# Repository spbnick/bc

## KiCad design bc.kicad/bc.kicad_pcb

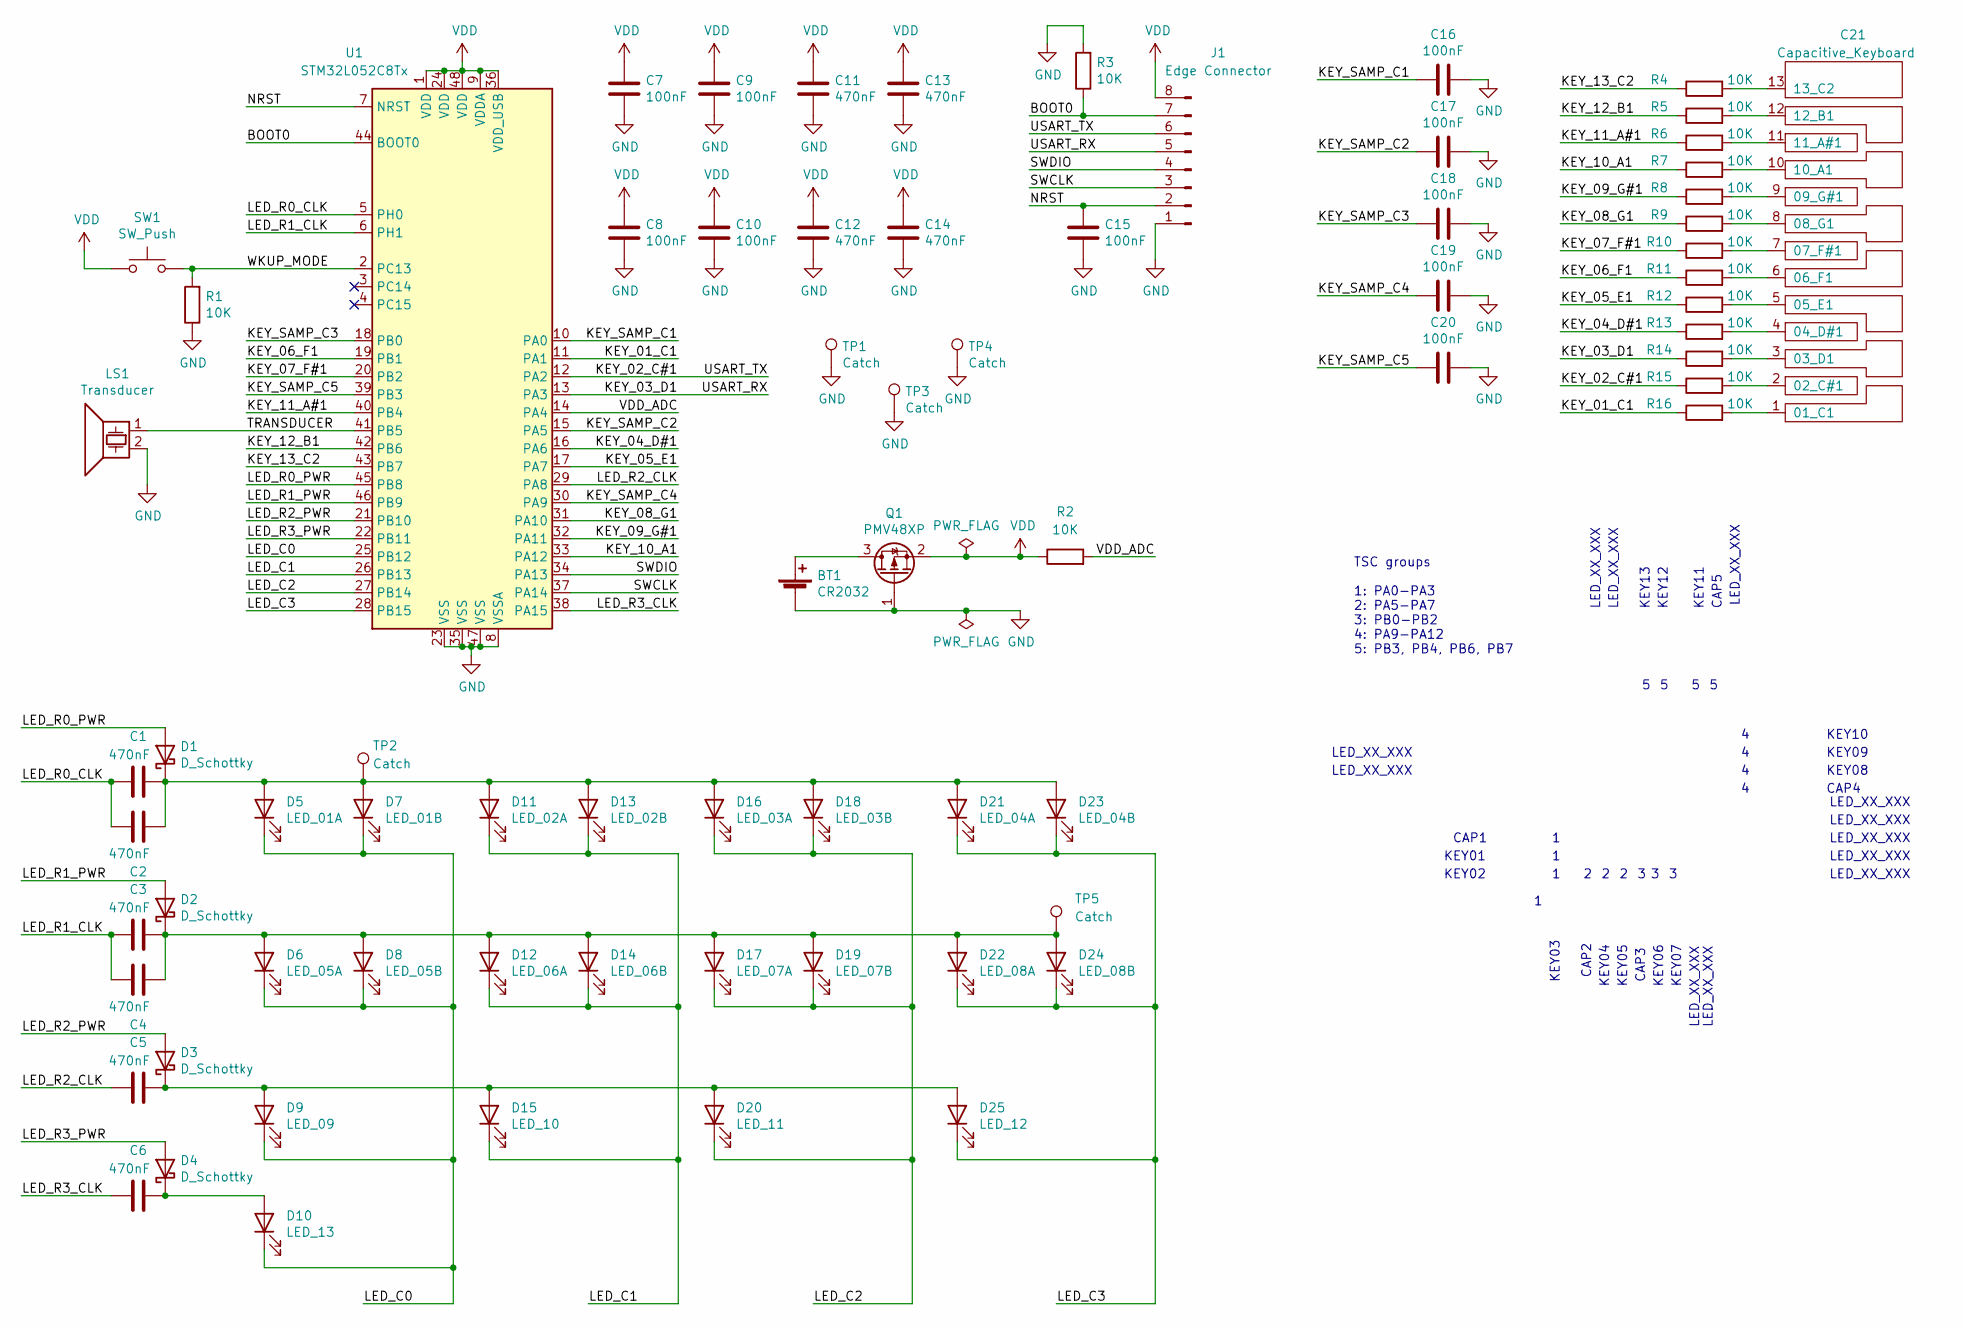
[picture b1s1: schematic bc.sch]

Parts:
BT1: CR2032; BatteryHolder_Keystone_3002_1x2032; LCSC C238099
C1, C2, C3, C4, C5, C6, C11, C12, C13, C14: 470nF; C_0402_1005Metric; LCSC C47339
C7, C8, C9, C10, C15, C16, C17, C18, C19, C20: 100nF; C_0402_1005Metric; LCSC C1525
C21: Capacitive_Keyboard; keyboard
D1, D2, D3, D4: D_Schottky; D_SOD-123; LCSC C8598
D5: LED_01A; side_led; Digi-Key 160-1870-1-ND
D6: LED_05A; side_led
D7: LED_01B; side_led
D8: LED_05B; side_led
D9: LED_09; side_led
D10: LED_13; side_led
D11: LED_02A; side_led
D12: LED_06A; side_led
D13: LED_02B; side_led
D14: LED_06B; side_led
D15: LED_10; side_led
D16: LED_03A; side_led
D17: LED_07A; side_led
D18: LED_03B; side_led
D19: LED_07B; side_led
D20: LED_11; side_led
D21: LED_04A; side_led
D22: LED_08A; side_led
D23: LED_04B; side_led
D24: LED_08B; side_led
D25: LED_12; side_led
J1: Edge Connector; edge_connector
LS1: Transducer; transducer; Digi-Key 668-1538-1-ND
Q1: PMV48XP; SOT-23; LCSC C75560
R1, R2, R3, R4, R5, R6, R7, R8, R9, R10, R11, R12, R13, R14, R15, R16: 10K; R_0402_1005Metric; LCSC C25744
SW1: SW_Push; SW_Push_1P1T_NO_5.1x5.1mm_H2.5mm; LCSC C318889
TP1, TP2, TP3, TP4, TP5: Catch; test_point; LCSC C238131
U1: STM32L052C8Tx; LQFP-48_7x7mm_P0.5mm; LCSC C111213

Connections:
/BOOT0: J1.7, R3.1, U1.44 (BOOT0)
/KEY_01_C1: R16.1, U1.11 (PA1)
/KEY_02_C#1: J1.6, R15.1, U1.12 (PA2)
/KEY_03_D1: J1.5, R14.1, U1.13 (PA3)
/KEY_04_D#1: R13.1, U1.16 (PA6)
/KEY_05_E1: R12.1, U1.17 (PA7)
/KEY_06_F1: R11.1, U1.19 (PB1)
/KEY_07_F#1: R10.1, U1.20 (PB2)
/KEY_08_G1: R9.1, U1.31 (PA10)
/KEY_09_G#1: R8.1, U1.32 (PA11)
/KEY_10_A1: R7.1, U1.33 (PA12)
/KEY_11_A#1: R6.1, U1.40 (PB4)
/KEY_12_B1: R5.1, U1.42 (PB6)
/KEY_13_C2: R4.1, U1.43 (PB7)
/KEY_SAMP_C1: C16.2, U1.10 (PA0)
/KEY_SAMP_C2: C17.2, U1.15 (PA5)
/KEY_SAMP_C3: C18.2, U1.18 (PB0)
/KEY_SAMP_C4: C19.2, U1.30 (PA9)
/KEY_SAMP_C5: C20.2, U1.39 (PB3)
/LED_C0: D5.1 (K), D6.1 (K), D7.1 (K), D8.1 (K), D9.1 (K), D10.1 (K), U1.25 (PB12)
/LED_C1: D11.1 (K), D12.1 (K), D13.1 (K), D14.1 (K), D15.1 (K), U1.26 (PB13)
/LED_C2: D16.1 (K), D17.1 (K), D18.1 (K), D19.1 (K), D20.1 (K), U1.27 (PB14)
/LED_C3: D21.1 (K), D22.1 (K), D23.1 (K), D24.1 (K), D25.1 (K), U1.28 (PB15)
/LED_R0_CLK: C1.1, C2.1, U1.5 (PH0)
/LED_R0_PWR: D1.2 (A), U1.45 (PB8)
/LED_R1_CLK: C3.1, C4.1, U1.6 (PH1)
/LED_R1_PWR: D2.2 (A), U1.46 (PB9)
/LED_R2_CLK: C5.1, U1.29 (PA8)
/LED_R2_PWR: D3.2 (A), U1.21 (PB10)
/LED_R3_CLK: C6.1, U1.38 (PA15)
/LED_R3_PWR: D4.2 (A), U1.22 (PB11)
/NRST: C15.1, J1.2, U1.7 (NRST)
/SWCLK: J1.3, U1.37 (PA14)
/SWDIO: J1.4, U1.34 (PA13)
/TRANSDUCER: LS1.1, U1.41 (PB5)
/VDD_ADC: R2.2, U1.14 (PA4)
/WKUP_MODE: R1.2, SW1.2, U1.2 (PC13)
GND: BT1.2 (-), C7.2, C8.2, C9.2, C10.2, C11.2, C12.2, C13.2, C14.2, C15.2, C16.1, C17.1, C18.1, C19.1, C20.1, J1.1, LS1.2, Q1.1 (G), R1.1, R3.2, TP1.1, TP3.1, TP4.1, U1.8 (VSSA), U1.23 (VSS), U1.35 (VSS), U1.47 (VSS)
unnamed: BT1.1 (+), Q1.3 (D)
unnamed: C1.2, C2.2, D1.1 (K), D5.2 (A), D7.2 (A), D11.2 (A), D13.2 (A), D16.2 (A), D18.2 (A), D21.2 (A), D23.2 (A), TP2.1
unnamed: C3.2, C4.2, D2.1 (K), D6.2 (A), D8.2 (A), D12.2 (A), D14.2 (A), D17.2 (A), D19.2 (A), D22.2 (A), D24.2 (A), TP5.1
unnamed: C5.2, D3.1 (K), D9.2 (A), D15.2 (A), D20.2 (A), D25.2 (A)
unnamed: C6.2, D4.1 (K), D10.2 (A)
unnamed: C21.1 (01_C1), R16.2
unnamed: C21.2 (02_C#1), R15.2
unnamed: C21.3 (03_D1), R14.2
unnamed: C21.4 (04_D#1), R13.2
unnamed: C21.5 (05_E1), R12.2
unnamed: C21.6 (06_F1), R11.2
unnamed: C21.7 (07_F#1), R10.2
unnamed: C21.8 (08_G1), R9.2
unnamed: C21.9 (09_G#1), R8.2
unnamed: C21.10 (10_A1), R7.2
unnamed: C21.11 (11_A#1), R6.2
unnamed: C21.12 (12_B1), R5.2
unnamed: C21.13 (13_C2), R4.2
VDD: C7.1, C8.1, C9.1, C10.1, C11.1, C12.1, C13.1, C14.1, J1.8, Q1.2 (S), R2.1, SW1.1, U1.1 (VDD), U1.9 (VDDA), U1.24 (VDD), U1.36 (VDD_USB), U1.48 (VDD)

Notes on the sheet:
KEY01
KEY02
KEY03
KEY04
KEY05
KEY06
KEY07
KEY08
KEY09
KEY10
KEY11
KEY12
KEY13
TSC groups 1: PA0-PA3 2: PA5-PA7 3: PB0-PB2 4: PA9-PA12 5: PB3, PB4, PB6, PB7
CAP1
CAP2
CAP3
CAP4
CAP5
LED_XX_XXX

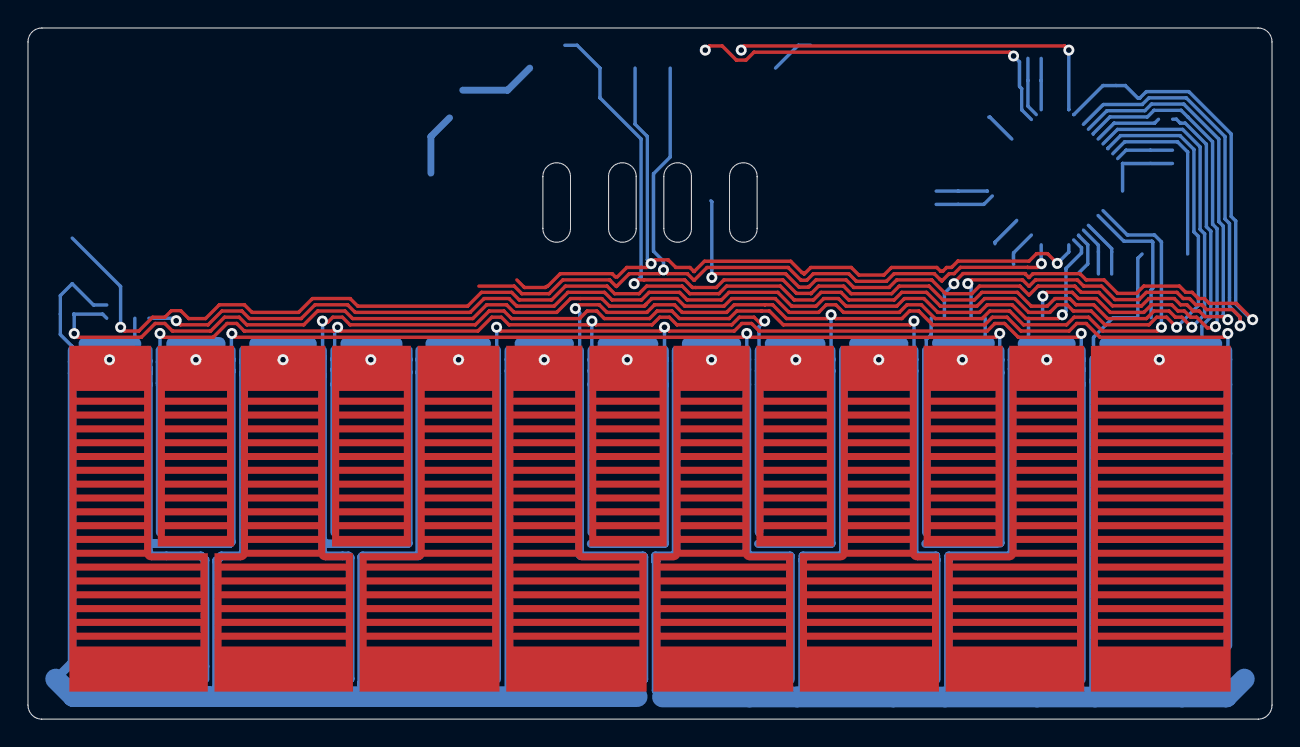
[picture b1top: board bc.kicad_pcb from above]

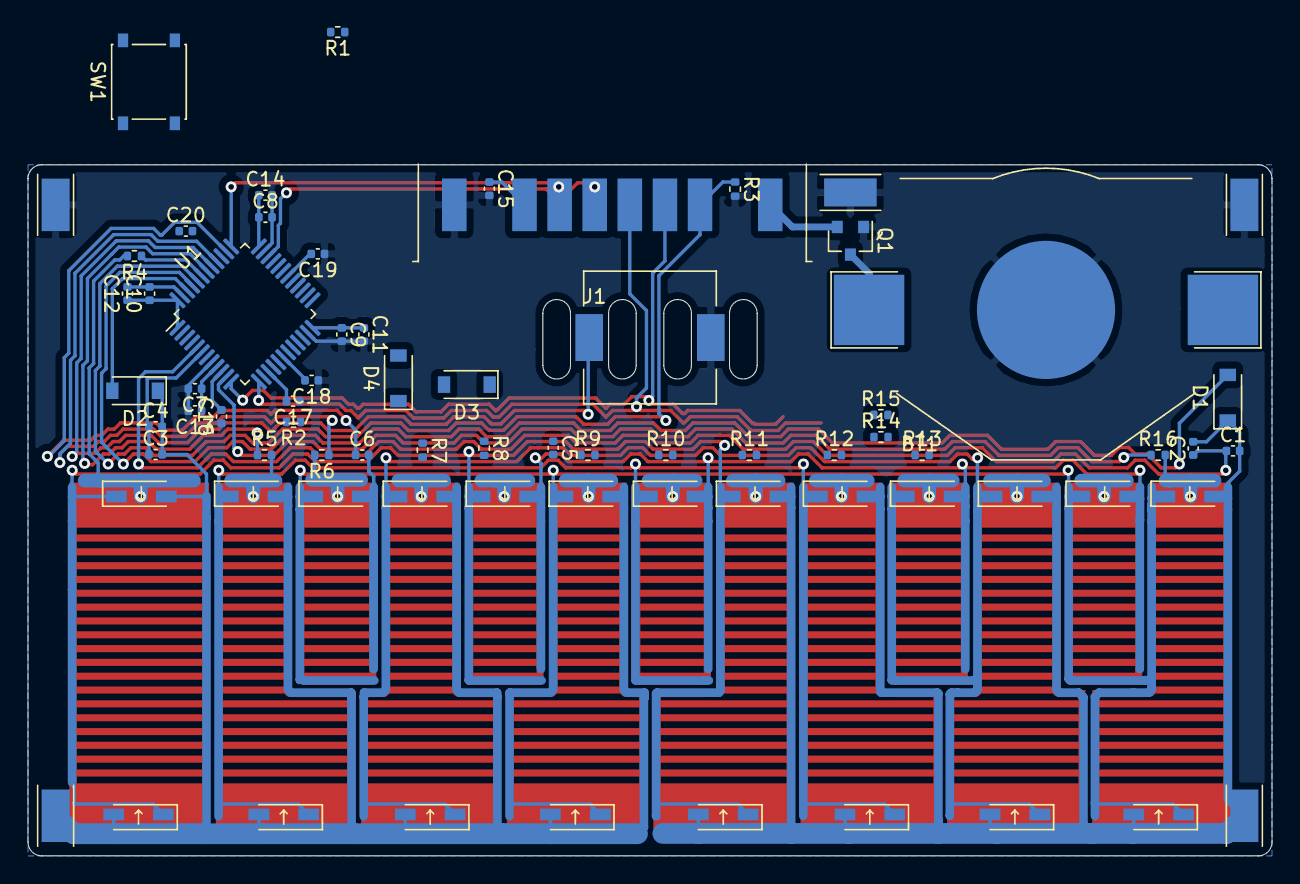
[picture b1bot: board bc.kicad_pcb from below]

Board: 2 copper layers, 90.0 x 50.0 mm, 73 parts (72 on the bottom side), 57 nets.

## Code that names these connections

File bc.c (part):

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static void
usart_init(void)
{
    /* Configure TX (PA14) and RX (PA15) pins */
    gpio_pin_conf_af(GPIO_A, 14, 4, GPIO_OTYPE_PUSH_PULL,
                     GPIO_PUPD_NONE, GPIO_OSPEED_HIGH);
    gpio_pin_conf_af(GPIO_A, 15, 4, GPIO_OTYPE_PUSH_PULL,
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/**
 * Configure the touch sense controller.
 * Use I/O Groups 4 and 5.
 * Group 4 (IO 1,3,4): PA9 - sampling cap, PA11, PA12 - sensors.
 * Group 5 (IO 1,2,3,4): PB3 - sampling cap, PB4, PB6, PB7 - sensors.
 */
static void
tsc_init(void)
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
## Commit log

2020-10-24 Add first Inkscape design draft
2020-10-25 Add roughly laid-out PoC PCB
2020-10-25 Fixup design draft a bit
2020-12-04 Experiment with keyboard backlighting
2020-12-04 Remove first PoC design files
2020-12-04 Switch from CR2016 to CR2032
2020-12-19 Verify touch sensing design
2020-12-21 Use GPIO helper functions for configuration
2020-12-21 Remove commented-out prototype code
2020-12-22 Validate LED control circuit
2020-12-24 Connect VDD to ADC
2020-12-24 Add bypassing to compensate for LED boosters
2020-12-26 Define some parts and footprints
2020-12-27 Assign all parts/footprints except keyboard
2020-12-28 Layout keyboard half draft
2021-01-05 Block as much light as possible between keys
2021-01-09 Attempt pasta plate routing on the front
